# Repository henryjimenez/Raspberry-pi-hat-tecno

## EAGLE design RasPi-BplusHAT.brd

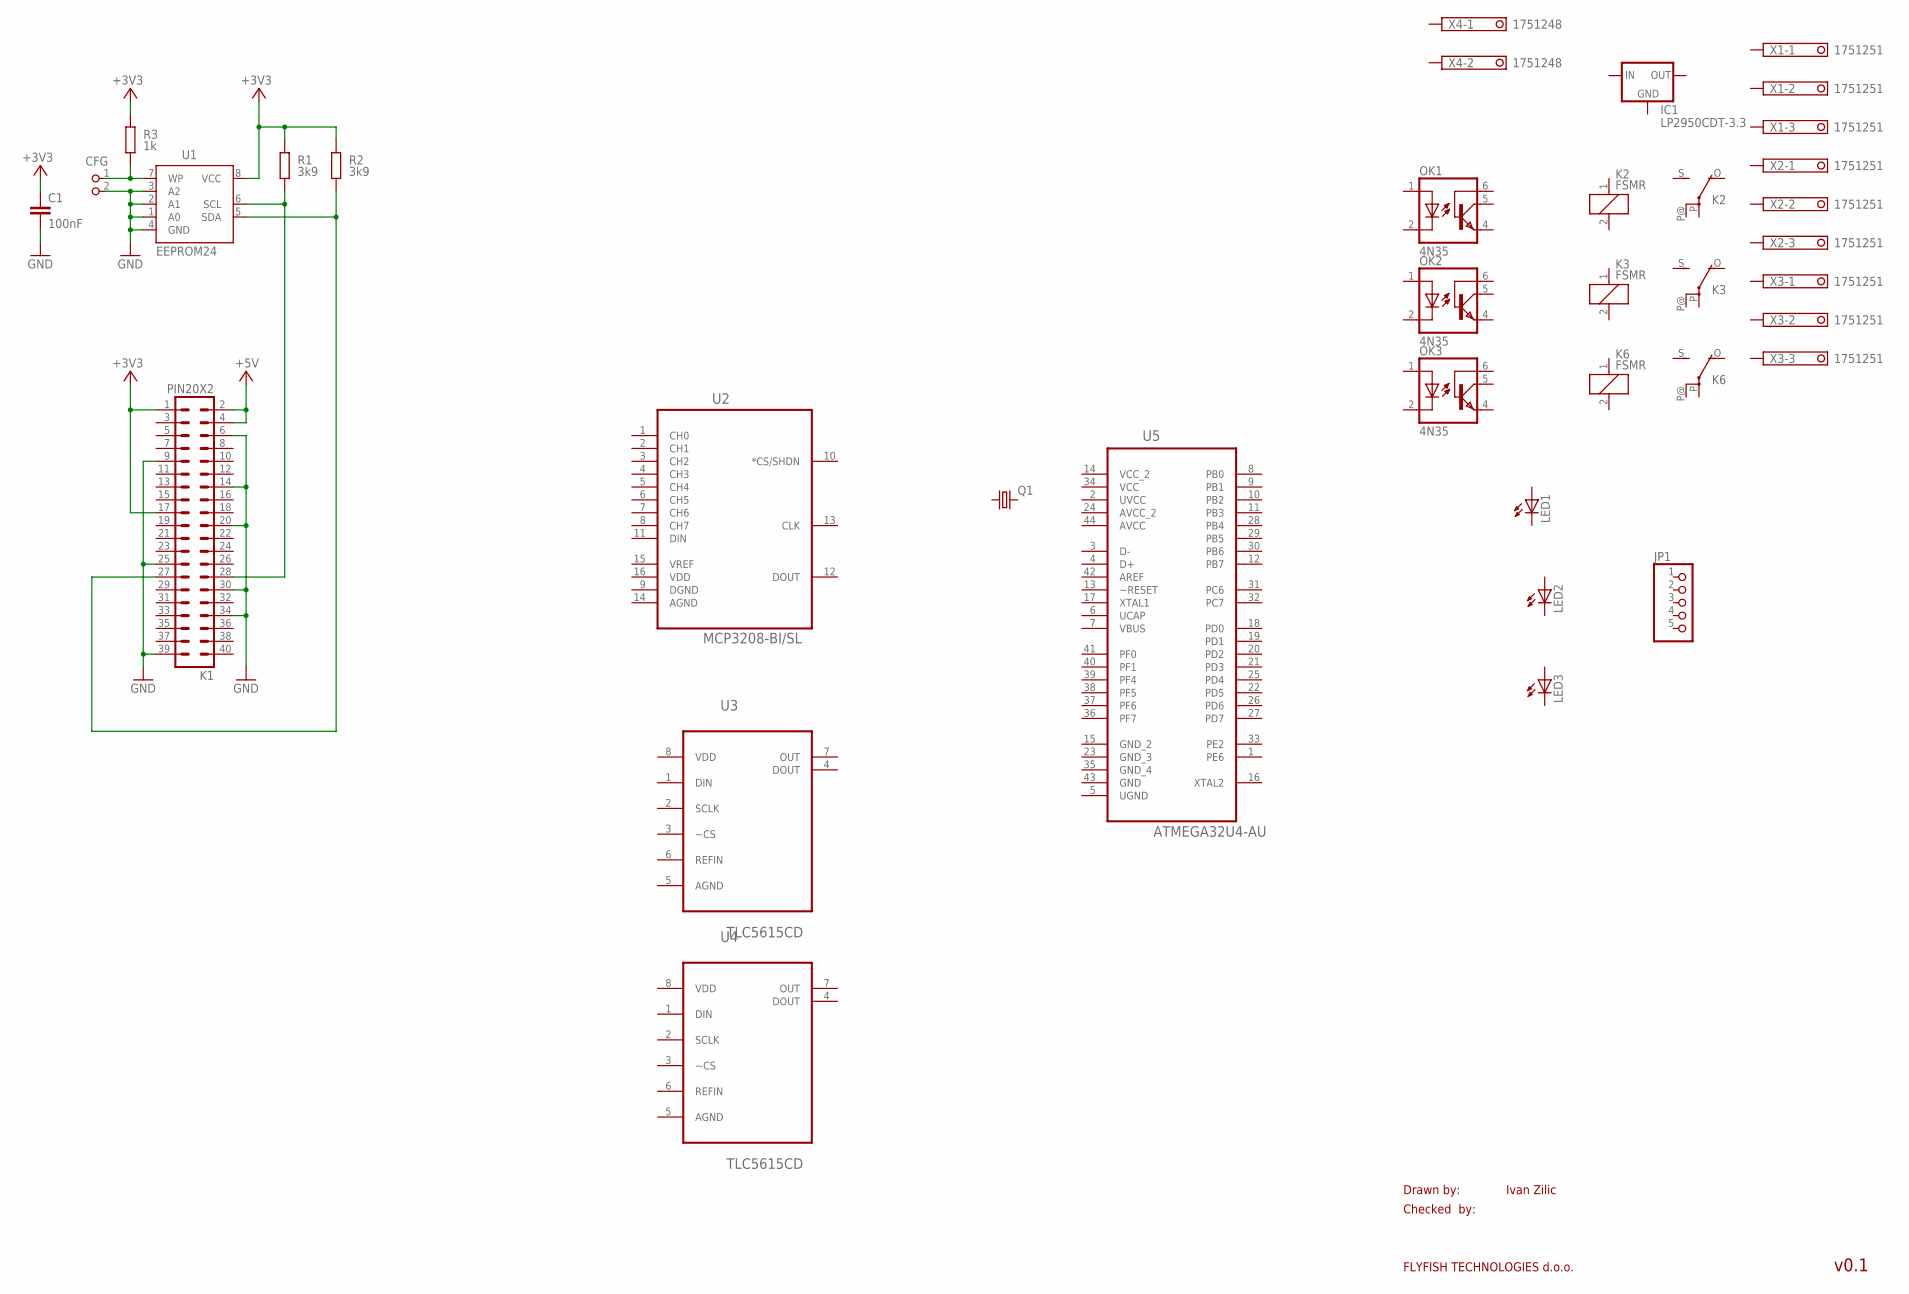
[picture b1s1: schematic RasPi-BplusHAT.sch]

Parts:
C1: 100nF; C0805K
CFG: PIN2_100; PIN_W_2
IC1: LP2950CDT-3.3; DPACK
JP1: PINHD-1X55X2MM; 1_05X2MM
K1: PIN20X2; PIN_20X2
K2, K3, K6: FSMR
LED1, LED2, LED3: LEDCHIPLED_1206; CHIPLED_1206
OK1, OK2, OK3: 4N35; DIL06
Q1: CRYSTALHC49UP; HC49UP
R1, R2: 3k9; M0805; TOLERANCE 5%
R3: 1k; M0805; TOLERANCE 5%
U1: EEPROM24; SOIC8
U2: MCP3208-BI/SL; SOIC127P600X175-16N
U3, U4: TLC5615CD; SOIC127P600X175-8N
U5: ATMEGA32U4-AU; QFP80P1200X1200X120-44N
X1, X2, X3: 1751251
X4: 1751248

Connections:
+3V3: C1.1, K1.1, K1.17, R1.2, R2.2, R3.2, U1.8 (VCC)
+5V: K1.2, K1.4
AVCC: U5.44 (AVCC)
AVCC_2: U5.24 (AVCC_2)
GND: C1.2, CFG.2, K1.6, K1.9, K1.14, K1.20, K1.25, K1.30, K1.34, K1.39, U1.1 (A0), U1.2 (A1), U1.3 (A2), U1.4 (GND)
unnamed: K1.28, R1.1, U1.6 (SCL)
unnamed: K1.27, R2.1, U1.5 (SDA)
unnamed: CFG.1, R3.1, U1.7 (WP)
UCAP: U5.6 (UCAP)
UVCC: U5.2 (UVCC)
VCC: U5.34 (VCC)
VCC_2: U5.14 (VCC_2)
VDD: U2.16 (VDD), U3.8 (VDD), U4.8 (VDD)

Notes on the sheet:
Drawn by:
Checked by:
FLYFISH TECHNOLOGIES d.o.o.
Ivan Zilic
v0.1

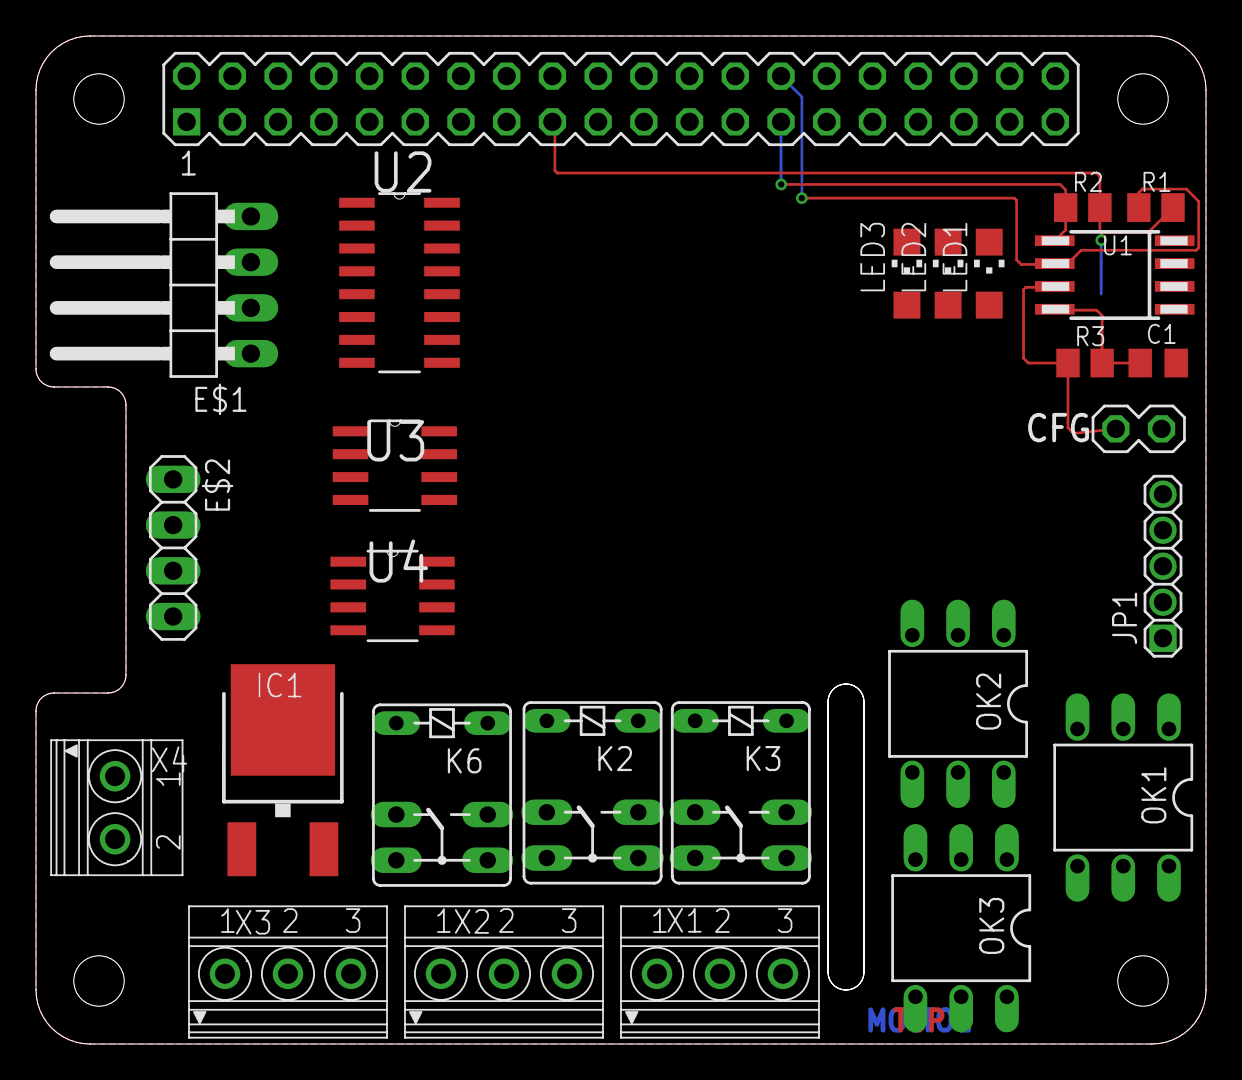
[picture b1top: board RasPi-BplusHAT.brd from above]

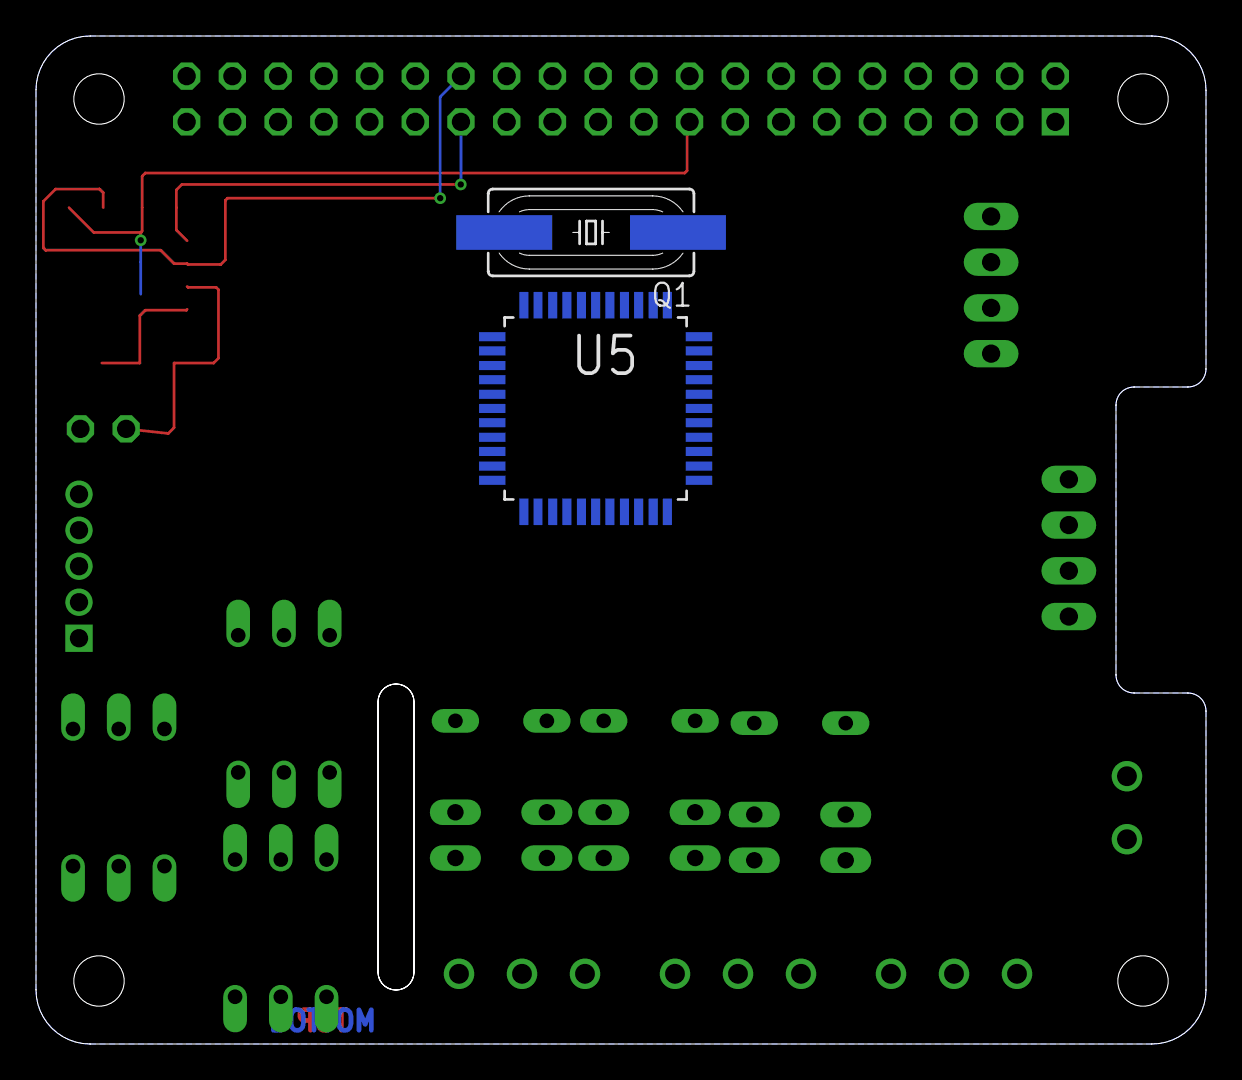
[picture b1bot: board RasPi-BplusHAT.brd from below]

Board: 2 copper layers, 65.0 x 56.0 mm, 29 parts (2 on the bottom side), 7 nets.

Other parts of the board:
E$1: 1X04/90
E$2: 1X04
